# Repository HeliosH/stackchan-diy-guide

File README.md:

# Stack-chan 国内自制指南

基于 [Stack-chan 社区 v1.1.0](https://github.com/stack-chan/stack-chan/tree/v1.1.0) 和 [M5Stack K151 官方资料](https://docs.m5stack.com/zh_CN/StackChan)整理。Stack-chan 用 M5Stack 屏幕显示表情，两只舵机构成双轴机身；社区固件使用 Moddable JavaScript/TypeScript 和 MOD。

**本版已修正接线、构建目标及舵机量程配置。自制路线完成了文档/源码核对和模拟协议测试，尚未完成实物整机验收。** 网页与 Markdown 同步生成；随附 PDF 为历史版本，电气、固件及采购操作以本版 Markdown 为准，不照旧 PDF 接线。

## 1. 选择路线

| 路线 | 主机/舵机 | 判断与前提 | 入口 |
|---|---|---|---|
| A 官方整机 | K151 原装核心及机身 | 厂家完整产品；按厂家使用说明操作 | [K151 整机](k151-kit-route/README.md) |
| B v1 + XL330 | CoreS3、XL330-M288-T×2 | 官方结构参考；需适配实际总线 GPIO 和自定义固件 | [XL330 路线](v1-xl330-route/README.md) |
| C v0 + SG90 | Core Basic/Gray 或 Core2、SG90×2 | 基础 DIY，先独立供电台架验证；显式选择 PWM | [SG90 路线](v0-sg90-route/README.md) |
| D SCS0009 | CoreS3 等、市售 SCS0009×2 | 合格半双工电路；需实测量程、raw 零位及限位 | [串行路线](scs0009-serial-route/README.md) |
| E K151 造型 | 普通 CoreS3、市售 SCS0009、官方 STL | 结构改造；不等价于 K151 专用电子方案，先试装支架 | [结构复刻](k151-body-route/README.md) |
| F 网页体验 | 不需要硬件 | 模拟器可验证软件，不能验证供电/接线/机构 | [网页工具](https://stack-chan.github.io/stack-chan/web/) |

先获得可用整机可选 A；学习 DIY 从 C 的小范围台架测试开始。B/D 在串行通信和标定通过后再合壳；E/G 等结构改造宜在基础机完成后进行。价格、现货、工具和 SMT 服务未实时核价，路线里的历史估算不作为采购承诺。

## 2. 接线与固件入口

**B/C/D/E 的完整配置、构建、烧录和无按键验收见 [DIY_FIRMWARE.md](DIY_FIRMWARE.md)。** 配套 `firmware-configs/` 提供按主机/接线区分的 JSON、SCS0009 raw 标定驱动及一次性小角度 MOD。

- CoreS3 GPIO16 用于摄像头，外部 Port.C 是17/18；不能沿用旧 Core 的17/16。
- CoreS3 厂商 M5-Bus 图中26脚是GPIO14，不是GND。按实际图确认真正地线并测通断。
- 串行 DATA 必须有正确半双工释放/接收时序。不用 RX 串二极管或普通 USB-TTL TX/RX 短接。
- 自制 CoreS3 构建通用 `m5stack_cores3`；官方 K151 才使用 `m5stackchan_cores3`。默认 `npm run flash/deploy` 是 K151，不读取自制机的 `manifest_local.json`。
- 原版 scservo 固定按200°换算、没有传递 `driver.serial`。本指南为市售300°型号提供 raw 标定驱动；确认配置和替换模块一起安装。
- 不要求 CoreS3 有 A/B/C 实体键；验收 MOD 用公开 setPose API 一次测试左右5°、上下3°及回中。

先不装摇臂、确认零位再装壳；舵机独立合适5V供电并共地，独立 +5V 不和主机 +5V 直接并接。扩大动作范围前测出机械干涉位置。K151 的 Y轴5-85°只适用于它的机械参考，自制机按实际零位、方向和机构限位。

## 3. PCB、打印与电源

| 模式 | 跳线 | GPIO/配置 |
|---|---|---|
| m5-pantilt 串行 | R13/R14；R9-R12 不装 | 按实际主机映射；CoreS3 为17/18 |
| PWM，旧 Core | R9/R11；串行跳线不装 | pan5 / tilt2 |
| PWM，Core2 | R10/R12；串行跳线不装 | pan19 / tilt27 |
| PWM，CoreS3 | R10/R12；串行跳线不装 | pan7 / tilt6 |

完整 KiCad 工程及 [制造文件](pcb/m5-pantilt-v1.0/manufacture/README.md)已附。`gerber/` 只有历史丝印/钻孔，不可作为完整制板输入；下单用 `manufacture/jlcpcb/` 内完整 Gerber ZIP。BOM/CPL 仍需在装配预览核对封装、极性、元件方向、跳线及 LCSC 匹配，未完成 DRC/ERC 和实板签核，不能宣称上传就可免核对制造。旧 PDF 原理图与当前 KiCad 的元件版本差异以实际制造基准处理。

STL 按 `stl/v1-xl330/`、`v0-sg90/`、`scs0009/`、`rs30x/`、`k151-body/`、`backpack/` 分类。先试装支架、舵机轴、轴承和主机卡位再整套打印。材料、支撑、强度和公差按实际打印条件选择，官方参考方向：

J5 是 BAT 电源路径，充电由具体主机管理，不是独立充电器。电池保护、极性、充电控制和升压路径需确认；不把 AAA/镍氢接到锂电充电端。容量不等于放电电流能力，初次采用桌面稳压电源并测压降。

## 4. 固件与进阶资料

离线 `firmware/stack-chan-firmware-v1.1.0.zip` 有四个目标的 bootloader、partition table 和应用。SHA-256 与随附校验文件一致、ZIP CRC 检查通过；未独立比对官方 release 下载件。此检查不证明预编译默认驱动和接线适合你的 DIY 机。

```bash
cd firmware
shasum -a 256 -c stack-chan-firmware-v1.1.0.zip.sha256
```

官方 K151 用网页工具选择 M5StackChan CoreS3 或专用离线目录；自制路线按 [自定义流程](DIY_FIRMWARE.md) 构建。恢复 K151 厂家出厂固件用 M5Burner。厂家 App 与社区 MOD 是两套生态，刷社区版会覆盖厂家版，普通 CoreS3 不能连接厂家 StackChan World App。

- [社区 API/MOD/TTS 文档存档及导读](firmware-docs/README.md)。
- [Hermes 桥接方案](hermes-integration/README.md)：机器人、语音桥接和 Agent API 分层；先验证 Mock/语音链路再接硬件。
- [官方产品及出厂固件](https://github.com/m5stack/StackChan)、[板级支持包](https://github.com/m5stack/StackChan-BSP)。
- [ROBOTIS XL330 规格与通信电路](https://emanual.robotis.com/docs/en/dxl/x/xl330-m288/)。
- 国内采购可从 [M5Stack 官方店](https://m5stack.taobao.com)、舵机厂家/授权代理、[嘉立创](https://www.jlc.com)及打印服务查询具体型号和实时价格。

## 5. 素材与许可

官方外壳、PCB、装配图、社区固件及文档来源为 [stack-chan/stack-chan](https://github.com/stack-chan/stack-chan)，许可 Apache-2.0。K151 结构来源为 [M5_Hardware](https://github.com/m5stack/M5_Hardware/tree/master/Products/K151_StackChan/Structures)，按该仓库对应许可核对；产品资料来自 M5Stack，SCS0009 规格书来自飞特。转载图片、数据手册及商品硬件不因本仓库的 LICENSE 自动变为同一许可。

本指南新增的配置、标定驱动、验收 MOD 和文档脚本按 Apache-2.0 发布。未修改官方存档源码/结构件或固件二进制。后续升级需重新核对 SDK、驱动接口和构建配置。

## 6. 重建网页与验证配套驱动

使用 Node.js 20 或更新版本，在本仓库执行：

```bash
npm ci --ignore-scripts
npm test
npm run docs:build
```

网页从上述路线 Markdown 自动生成，避免接线说明在两份文档里分叉。测试使用模拟舵机协议，检查 raw 角度换算、机械限位、串口传递及错误处理，不代替设备构建和实机测试。PDF 不参与此生成流程。

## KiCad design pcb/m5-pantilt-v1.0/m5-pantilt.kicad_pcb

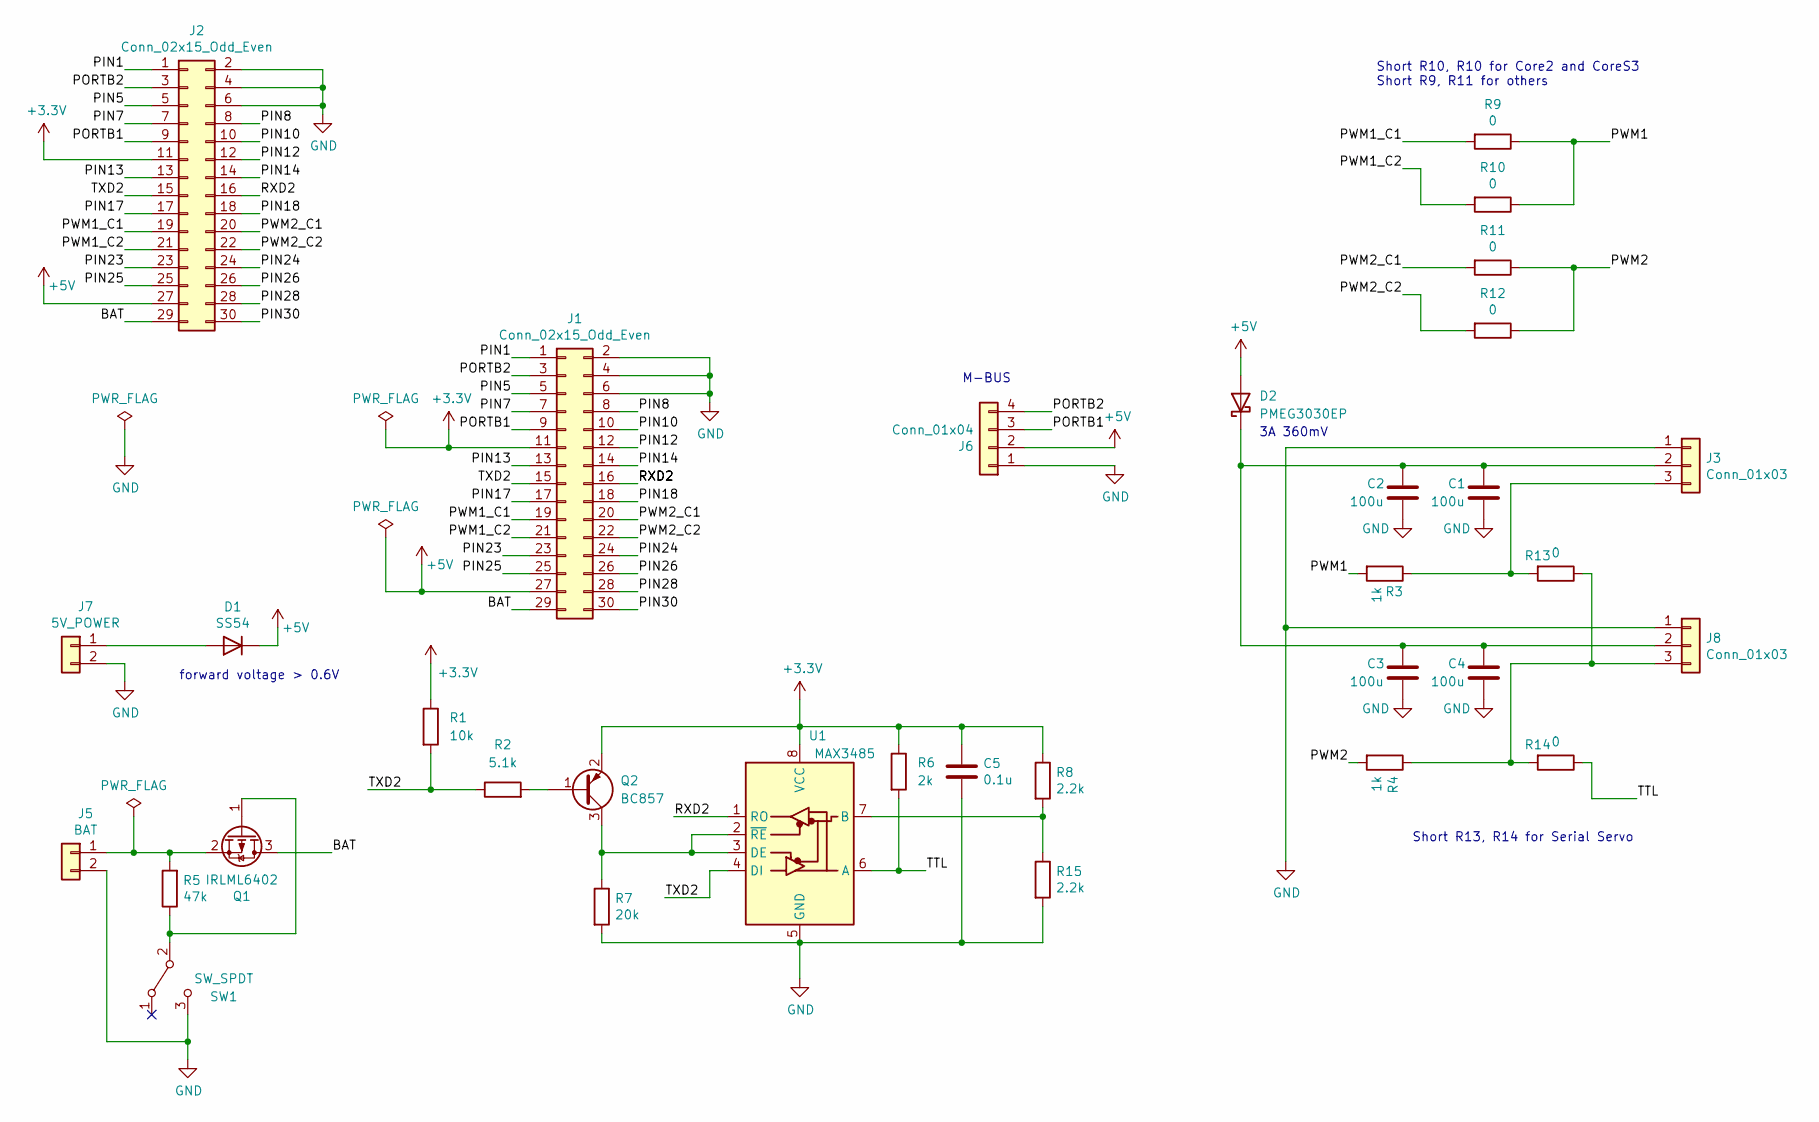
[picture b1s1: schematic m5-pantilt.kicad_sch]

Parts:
C1, C2, C3, C4: 100u; C_1206_3216Metric_Pad1.33x1.80mm_HandSolder; LCSC C15008
C5: 0.1u; C_0603_1608Metric; LCSC C14663
D1: SS54; D_SMA; LCSC C2931790
D2: PMEG3030EP; D_SOD-128; LCSC C255587
J1: Conn_02x15_Odd_Even; PinHeader_2x15_P2.54mm_Vertical_SMD
J2: Conn_02x15_Odd_Even; PinSocket_2x15_P2.54mm_Vertical_SMD
J3, J8: Conn_01x03; JST_EH_B3B-EH-A_1x03_P2.50mm_Vertical
J5: BAT; JST_PH_B2B-PH-K_1x02_P2.00mm_Vertical; LCSC C2319
J6: Conn_01x04; JST_PH_S4B-PH-K_1x04_P2.00mm_Horizontal
J7: 5V_POWER; JST_XH_B2B-XH-A_1x02_P2.50mm_Vertical; LCSC C20079
Q1: IRLML6402; SOT-23; LCSC C2886430
Q2: BC857; SOT-23_Mirrored; LCSC C2139
R1: 10k; R_0603_1608Metric_Mirrored; LCSC C25804
R2: 5.1k; R_0603_1608Metric_Mirrored; LCSC C23186
R3, R4: 1k; R_0603_1608Metric_Pad0.98x0.95mm_HandSolder; LCSC C21190
R5: 47k; R_0603_1608Metric_Pad0.98x0.95mm_HandSolder_Mirrored; LCSC C25819
R6: 2k; R_0603_1608Metric; LCSC C22975
R7: 20k; R_0603_1608Metric; LCSC C4184
R8, R15: 2.2k; R_0603_1608Metric; LCSC C4190
R9, R10, R11, R12: 0; R_0603_1608Metric_Pad0.98x0.95mm_HandSolder; LCSC C21189
R13, R14: 0; R_0603_1608Metric; LCSC C21189
SW1: SW_SPDT; SW_CuK_OS102011MA1QN1_SPDT_Angled
U1: MAX3485; SOIC-8_3.9x4.9mm_P1.27mm; LCSC C668204

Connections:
+3V3: C5.1, J1.11, J2.11, Q2.2 (E), R1.1, R6.1, R8.1, U1.8 (VCC)
+5V: D1.1 (K), D2.2 (A), J1.27, J2.27, J6.2
/BAT: J1.29, J2.29, Q1.3 (D)
/PIN1: J1.1, J2.1
/PIN5: J1.5, J2.5
/PIN7: J1.7, J2.7
/PIN8: J1.8, J2.8
/PIN10: J1.10, J2.10
/PIN12: J1.12, J2.12
/PIN13: J1.13, J2.13
/PIN14: J1.14, J2.14
/PIN17: J1.17, J2.17
/PIN18: J1.18, J2.18
/PIN23: J1.23, J2.23
/PIN24: J1.24, J2.24
/PIN25: J1.25, J2.25
/PIN26: J1.26, J2.26
/PIN28: J1.28, J2.28
/PIN30: J1.30, J2.30
/PORTB1: J1.9, J2.9, J6.3
/PORTB2: J1.3, J2.3, J6.4
/PWM1: R3.2, R9.1, R10.1
/PWM1_C1: J1.19, J2.19, R9.2
/PWM1_C2: J1.21, J2.21, R10.2
/PWM2: R4.2, R11.1, R12.1
/PWM2_C1: J1.20, J2.20, R11.2
/PWM2_C2: J1.22, J2.22, R12.2
/RXD2: J1.16, J2.16, U1.1 (RO)
/TTL: R6.2, R14.1, U1.6 (A)
/TXD2: J1.15, J2.15, R1.2, R2.1, U1.4 (DI)
GND: C1.1, C2.1, C3.2, C4.1, C5.2, J1.2, J1.4, J1.6, J2.2, J2.4, J2.6, J3.1, J5.2, J6.1, J7.2, J8.1, R7.2, R15.2, SW1.3 (C), U1.5 (GND)
unnamed: D1.2 (A), J7.1
unnamed: C1.2, C2.2, C3.1, C4.2, D2.1 (K), J3.2, J8.2
unnamed: J3.3, R3.1, R13.2
unnamed: J5.1, Q1.2 (S), R5.2
unnamed: J8.3, R4.1, R13.1, R14.2
unnamed: Q1.1 (G), R5.1, SW1.2 (B)
unnamed: Q2.1 (B), R2.2
unnamed: Q2.3 (C), R7.1, U1.2 (~RE), U1.3 (DE)
unnamed: R8.2, R15.1, U1.7 (B)

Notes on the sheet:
M-BUS
Short R13, R14 for Serial Servo
forward voltage > 0.6V
3A 360mV
Short R10, R10 for Core2 and CoreS3 Short R9, R11 for others

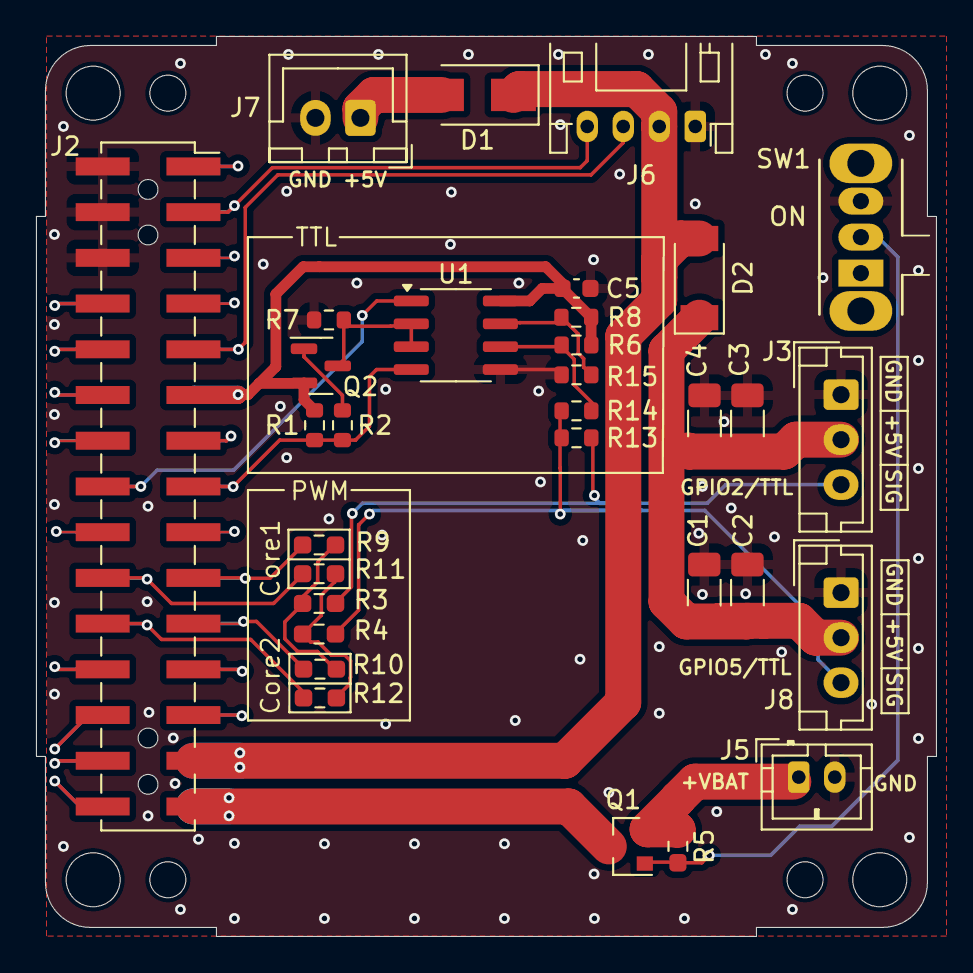
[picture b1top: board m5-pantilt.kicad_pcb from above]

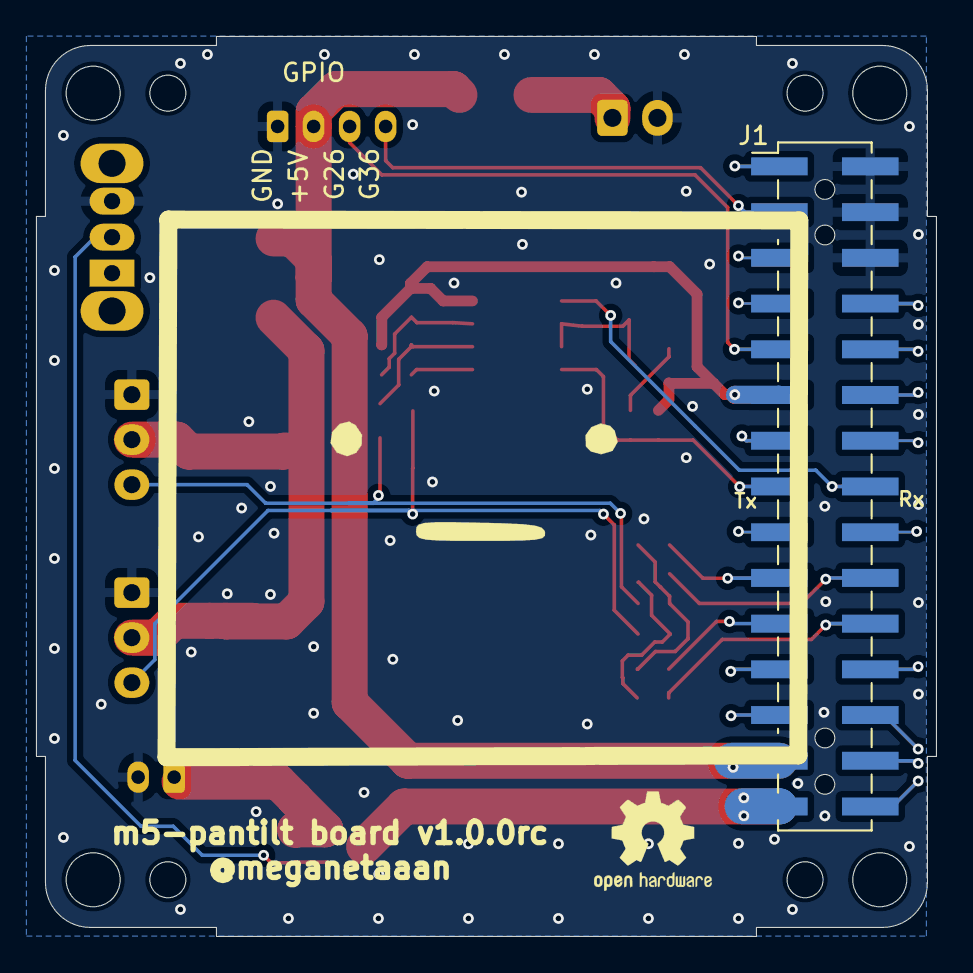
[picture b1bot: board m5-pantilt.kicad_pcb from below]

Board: 2 copper layers, 50.0 x 50.0 mm, 38 parts (2 on the bottom side), 40 nets.

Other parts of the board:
Hole1, Hole2, Hole3, Hole4: mountinghole_M2_M3
LOGO: LOGO; avatar_small

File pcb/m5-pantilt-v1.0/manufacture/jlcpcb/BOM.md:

# m5-pantilt v1.0 元件清单

> LCSC 编号来自官方原理图元件库 + 本仓库补充核实（J3/J8、J6 为 2026-10 经嘉立创元件库逐一验证的原厂 JST 料）；**匹配编号后仍须检查实际型号/封装，是否可机器装配以嘉立创当前服务为准**。
> `SMD 可贴` = 嘉立创 SMT 可贴装；`THT 手焊` = 通孔件到手手焊；`来料` = 不在默认商城清单，自购后手焊；完整代工清单则列入客户供料，由工厂另安排装配。**LOGO 丝印图形不是元件。**

## 一、贴片订单内（SMT，随 PCB 一起贴）

| 位号 | 值 | 封装 | LCSC | 装配 |
|---|---|---|---|---|
| C1,C2,C3,C4 | 100µ | C_1206_3216Metric_Pad1.33x1.80mm_HandSolder | C15008 | SMD 可贴 |
| C5 | 0.1µ | C_0603_1608Metric | C14663 | SMD 可贴 |
| D1 | SS54 | D_SMA | C2931790 | SMD 可贴 |
| D2 | PMEG3030EP | D_SOD-128 | C255587 | SMD 可贴 |
| Q1 | IRLML6402 | SOT-23 | C2886430 | SMD 可贴 |
| Q2 | BC857 | SOT-23 | C2139 | SMD 可贴 |
| R1 | 10k | R_0603_1608Metric | C25804 | SMD 可贴 |
| R2 | 5.1k | R_0603_1608Metric | C23186 | SMD 可贴 |
| R3,R4 | 1k | R_0603_1608Metric_Pad0.98x0.95mm_HandSolder | C21190 | SMD 可贴 |
| R5 | 47k | R_0603_1608Metric_Pad0.98x0.95mm_HandSolder | C25819 | SMD 可贴 |
| R6 | 2k | R_0603_1608Metric | C22975 | SMD 可贴 |
| R7 | 20k | R_0603_1608Metric | C4184 | SMD 可贴 |
| R8,R15 | 2.2k | R_0603_1608Metric | C4190 | SMD 可贴 |
| **R13,R14** | **0Ω** | R_0603_1608Metric | C21189 | SMD 可贴（串行舵机版必装） |
| U1 | MAX3485 | **SOIC-8_3.9x4.9mm_P1.27mm（窄体）** | C668204 | SMD 可贴 |

> **R9–R12（0Ω）不在贴装清单里**：它们是 PWM/SG90 版的 Core 型号选择跳线（Core Basic/Gray 短 R9+R11，Core2/CoreS3 短 R10+R12）。串行舵机版（本路线默认）**不装**。如果你做 PWM 版，自行购买 0603 0Ω 手焊即可（LCSC C21189）。

## 二、通孔件（有料号，另安排采购与插件焊接或到手手焊）

| 位号 | 值 | 封装 | LCSC | 说明 |
|---|---|---|---|---|
| J3,J8 | Conn_01x03 | JST EH B3B-EH-A（通孔直立 2.5mm） | **C160259** | 舵机口 ×2（JST 原厂） |
| J5 | BAT | JST PH B2B-PH-K（通孔直立 2.0mm） | C2319 | 电池口（Boom Precision PH-2A） |
| J6 | Conn_01x04 | JST PH S4B-PH-K（通孔侧入 2.0mm） | **C157926** | PH 4pin（JST 原厂，侧入式） |
| J7 | 5V_POWER | JST XH B2B-XH-A（通孔直立 2.5mm） | C20079 | 5V 外供电口 |

## 三、来料/自备件（不在 SMT 订单里，自购后手焊）

| 位号 | 规格 | 采购建议 |
|---|---|---|
| J1 | 2×15 P2.54 **贴片**排针（焊在背面 Bottom） | M-BUS 引出。采购 **2×15、P2.54、直立 SMD** 排针，按 PCB 焊盘及机身空间核对尺寸；不能用单排通孔排针裁切替代（[C2337 实际为通孔 1×40](https://www.lcsc.com/product-detail/C2337.html)）。采购前核对下方焊盘尺寸 |
| J2 | 2×15 P2.54 **贴片**排母 | M5Stack 主机插这里。采购 **2×15、P2.54、直立 SMD** 排母；针脚形状和排母高度必须与 PCB 焊盘、主机和外壳匹配，不能仅凭“2x15”选择通孔排母 |
| SW1 | C&K OS102011MA1QN1（SPDT 侧拨，弯脚） | LCSC 在售直脚版 OS102011MS2QN1（C221829），**封装不同不能直接换**；弯脚原版建议淘宝购 C&K 原厂或国产同尺寸仿品（搜"OS102011"） |

> J1/J2 官方原理图也未指定料号（M-BUS 连接器高度随机箱结构而定），故按来料处理。
> **LOGO 丝印图形不是元件**；Hole1–Hole4 为安装孔，不在贴装坐标（CPL）内。

### 自备件焊盘尺寸与装配验收

下表直接取自本仓库 PCB。P2.54 指相邻触点节距；两列 SMD 焊盘中心距约 5.05mm，**不是触点排距**。让供应商提供底部焊脚尺寸图，并确认脚位编号、针高和机身空间；未确认的连接器不能用“同针数”自动替换。

| 位号 | 装配面 | PCB 焊盘要求 | 数量/板 |
|---|---|---|---|
| J1 | Bottom，直立 SMD 排针 | 2×15；纵向节距 2.54mm；焊盘两列中心距 5.05mm；每焊盘 3.15×1.00mm | 1 |
| J2 | Top，直立 SMD 排母 | 2×15；纵向节距 2.54mm；焊盘两列中心距 5.04mm；每焊盘 3.00×1.00mm | 1 |
| SW1 | Top，侧拨通孔开关 | 3 个信号脚节距 2.00mm / 孔径 0.90mm；两固定脚 x=-2.10 / +6.10mm、孔径 1.50mm；型号 OS102011MA1QN1 | 1 |

完整代工的 29 件 BOM 和双面坐标见 [制造说明](../README.md#完整代工需补充的材料)。J1/J2 的实际采购型号与高度仍须按尺寸图和主机/外壳试装确认；本表给出匹配条件，不声称已完成实物签核。
